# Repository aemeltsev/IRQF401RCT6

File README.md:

License
-------

IRQF401RCT6 schematic files and documentations are distributed under 
Creative Commons Attribution 4.0 International License.

Overview
--------
Simply dev. board based STM32F401RCT6. And includes in self: i2c eeprom memory and RS485 transceiver ic.

![PCB image][pcb_ray]

[pcb_ray]: https://github.com/aemeltsev/IRQF401RCT6/blob/master/doc/pcb_ray.png

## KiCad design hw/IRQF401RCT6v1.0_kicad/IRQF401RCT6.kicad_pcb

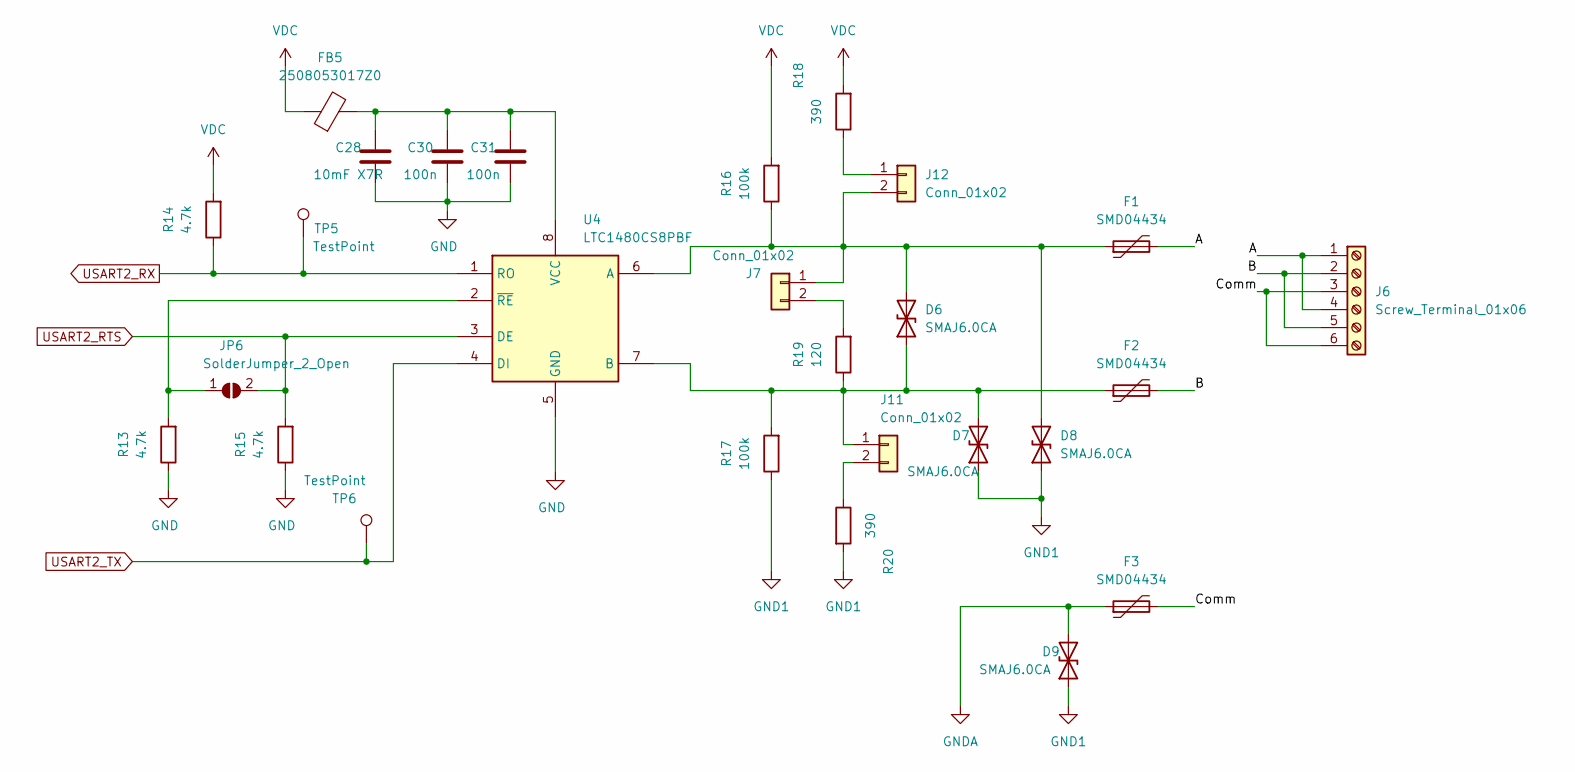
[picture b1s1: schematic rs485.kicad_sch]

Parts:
C28: 10mF X7R; C_1206_3216Metric
C30, C31: 100n; C_0805_2012Metric
D6, D7, D8, D9: SMAJ6.0CA; D_SMA
F1, F2, F3: SMD04434; Fuse_1812_4532Metric
FB5: 2508053017Z0; L_0805_2012Metric
J6: Screw_Terminal_01x06; PhoenixContact_MC_1,5_6-G-3.81_1x06_P3.81mm_Horizontal
J7, J11, J12: Conn_01x02; PinHeader_1x02_P2.54mm_Vertical
JP6: SolderJumper_2_Open; SolderJumper-2_P1.3mm_Open_TrianglePad1.0x1.5mm
R13, R14, R15: 4.7k; R_0805_2012Metric
R16, R17: 100k; R_0805_2012Metric
R18, R20: 390; R_0805_2012Metric
R19: 120; R_0805_2012Metric
TP5, TP6: TestPoint; TestPoint_Pad_D1.0mm
U4: LTC1480CS8PBF; SOIC-8_3.9x4.9mm_P1.27mm; Manufacturer_Part_Number LTC1480CS8PBF

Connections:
/RS485/A: F1.2, J6.1, J6.4
/RS485/B: F2.2, J6.2, J6.5
/RS485/Comm: F3.2, J6.3, J6.6
GND: C28.2, C30.2, C31.2, R13.1, R15.1, U4.5 (GND); also elsewhere on the board
GND1: D7.1 (A1), D8.1 (A1), D9.1 (A1), R17.1, R20.2
GNDA: D9.2 (A2), F3.1; also elsewhere on the board
unnamed: C28.1, C30.1, C31.1, FB5.2, U4.8 (VCC)
unnamed: D6.1 (A1), D7.2 (A2), F2.1, J11.1, R17.2, R19.1, U4.7 (B)
unnamed: D6.2 (A2), D8.2 (A2), F1.1, J7.1, J12.2, R16.1, U4.6 (A)
unnamed: J7.2, R19.2
unnamed: J11.2, R20.1
unnamed: J12.1, R18.1
unnamed: JP6.1 (A), R13.2, U4.2 (~RE)
USART2_RTS: JP6.2 (B), R15.2, U4.3 (DE); also elsewhere on the board
USART2_RX: R14.1, TP5.1, U4.1 (RO); also elsewhere on the board
USART2_TX: TP6.1, U4.4 (DI); also elsewhere on the board
VDC: FB5.1, R14.2, R16.2, R18.2; also elsewhere on the board

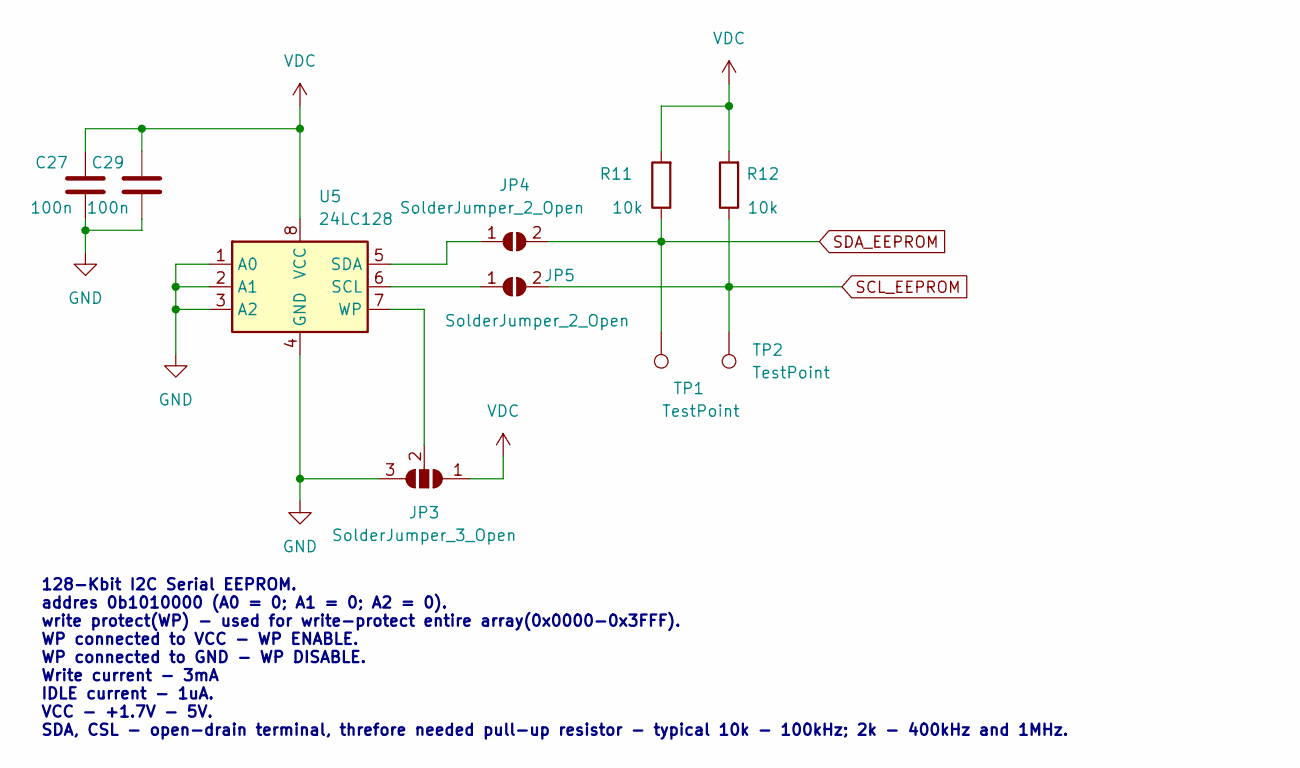
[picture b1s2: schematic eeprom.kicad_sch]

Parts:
C27, C29: 100n; C_0805_2012Metric
JP3: SolderJumper_3_Open; SolderJumper-3_P1.3mm_Open_RoundedPad1.0x1.5mm_NumberLabels
JP4, JP5: SolderJumper_2_Open; SolderJumper-2_P1.3mm_Open_TrianglePad1.0x1.5mm
R11, R12: 10k; R_0805_2012Metric
TP1, TP2: TestPoint; TestPoint_Pad_D1.0mm
U5: 24LC128; SOIC-8_3.9x4.9mm_P1.27mm

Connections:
GND: C27.2, C29.2, JP3.3 (B), U5.1 (A0), U5.2 (A1), U5.3 (A2), U5.4 (GND); also elsewhere on the board
unnamed: JP3.2 (C), U5.7 (WP)
unnamed: JP4.1 (A), U5.5 (SDA)
unnamed: JP5.1 (A), U5.6 (SCL)
SCL_EEPROM: JP5.2 (B), R12.1, TP2.1; also elsewhere on the board
SDA_EEPROM: JP4.2 (B), R11.1, TP1.1; also elsewhere on the board
VDC: C27.1, C29.1, JP3.1 (A), R11.2, R12.2, U5.8 (VCC); also elsewhere on the board

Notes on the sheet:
128-Kbit I2C Serial EEPROM. addres 0b1010000 (A0 = 0; A1 = 0; A2 = 0). write protect(WP) - used for write-protect entire array(0x0000-0x3FFF). WP connected to VCC - WP ENABLE. WP connected to GND - WP DISABLE. Write current - 3mA IDLE current - 1uA. VCC - +1.7V - 5V. SDA, CSL - open-drain terminal,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

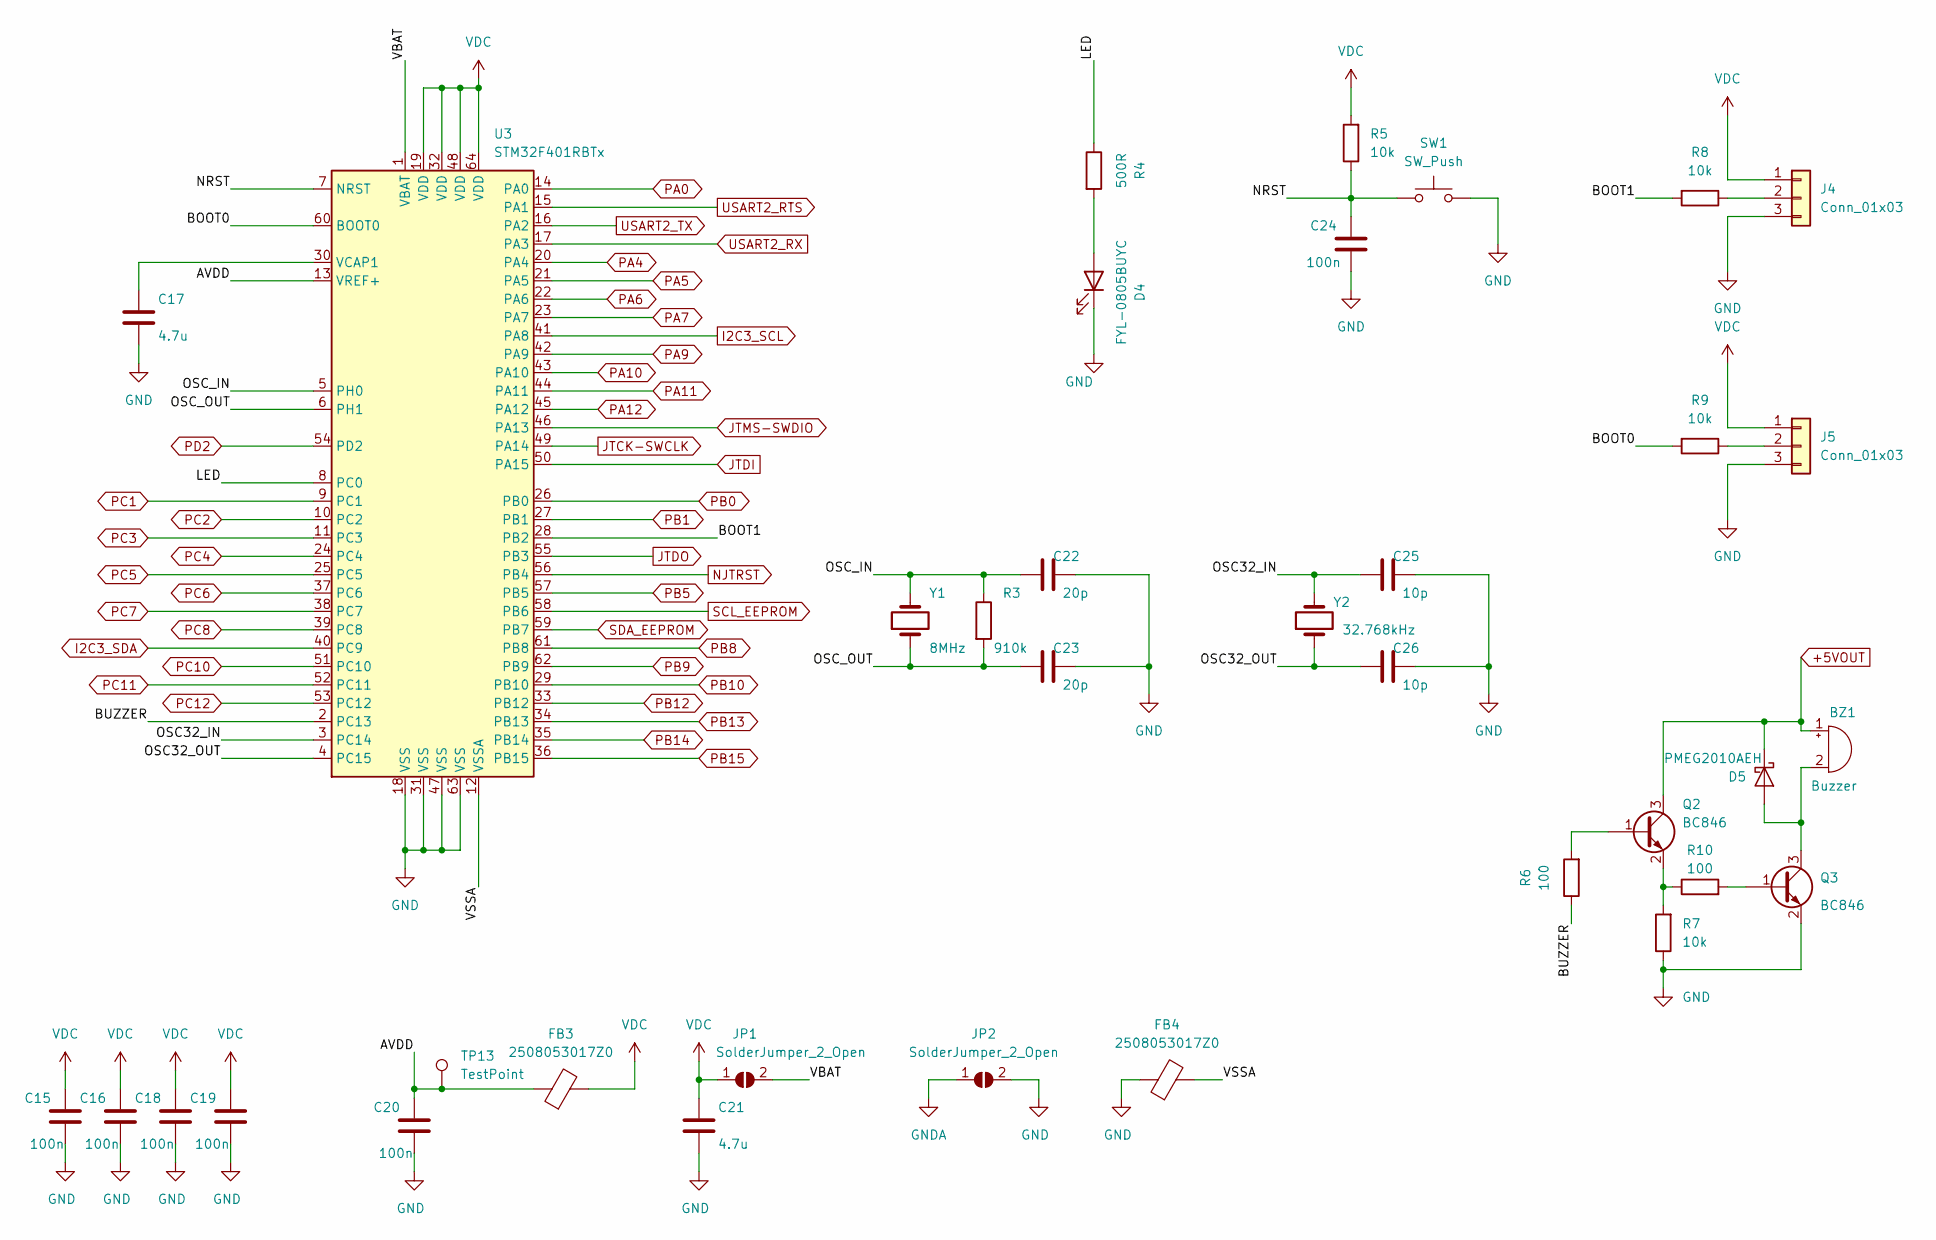
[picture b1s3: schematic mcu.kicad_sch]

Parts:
BZ1: Buzzer; Buzzer_12x9.5RM7.6
C15, C16, C18, C19, C20, C24: 100n; C_0805_2012Metric
C17, C21: 4.7u; C_1206_3216Metric
C22, C23: 20p; C_0805_2012Metric
C25, C26: 10p; C_0805_2012Metric
D4: FYL-0805BUYC; LED_0805_2012Metric
D5: PMEG2010AEH; D_SOD-123F
FB3, FB4: 2508053017Z0; L_0805_2012Metric
J4, J5: Conn_01x03; PinHeader_1x03_P2.54mm_Vertical
JP1, JP2: SolderJumper_2_Open; SolderJumper-2_P1.3mm_Open_TrianglePad1.0x1.5mm
Q2, Q3: BC846; SOT-23
R3: 910k; R_0805_2012Metric
R4: 500R; R_0805_2012Metric
R5, R7, R8, R9: 10k; R_0805_2012Metric
R6, R10: 100; R_0805_2012Metric
SW1: SW_Push; SW_DIP_SPSTx01_Slide_6.7x4.1mm_W7.62mm_P2.54mm_LowProfile
TP13: TestPoint; TestPoint_Pad_D1.0mm
U3: STM32F401RBTx; LQFP-64_10x10mm_P0.5mm
Y1: 8MHz; Crystal_HC49-4H_Vertical
Y2: 32.768kHz; Crystal_C26-LF_D2.1mm_L6.5mm_Horizontal_1EP_style1

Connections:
+5VOUT: BZ1.1 (-), D5.1 (K), Q2.3 (C); also elsewhere on the board
/MCU/AVDD: C20.1, FB3.1, TP13.1, U3.13 (VREF+)
/MCU/BOOT0: R9.2, U3.60 (BOOT0)
/MCU/BOOT1: R8.2, U3.28 (PB2)
/MCU/BUZZER: R6.1, U3.2 (PC13)
/MCU/LED: R4.1, U3.8 (PC0)
/MCU/NRST: C24.1, R5.1, SW1.1, U3.7 (NRST)
/MCU/OSC32_IN: C25.1, U3.3 (PC14), Y2.2
/MCU/OSC32_OUT: C26.1, U3.4 (PC15), Y2.1
/MCU/OSC_IN: C22.1, R3.1, U3.5 (PH0), Y1.2
/MCU/OSC_OUT: C23.1, R3.2, U3.6 (PH1), Y1.1
/MCU/VBAT: JP1.2 (B), U3.1 (VBAT)
/MCU/VSSA: FB4.2, U3.12 (VSSA)
GND: C15.2, C16.2, C17.2, C18.2, C19.2, C20.2, C21.2, C22.2, C23.2, C24.2, C25.2, C26.2, D4.1 (K), FB4.1, J4.3, J5.3, JP2.2 (B), Q3.2 (E), R7.1, SW1.2, U3.18 (VSS), U3.31 (VSS), U3.47 (VSS), U3.63 (VSS); also elsewhere on the board
GNDA: JP2.1 (A); also elsewhere on the board
I2C3_SCL: U3.41 (PA8); also elsewhere on the board
I2C3_SDA: U3.40 (PC9); also elsewhere on the board
JTCK-SWCLK: U3.49 (PA14); also elsewhere on the board
JTDI: U3.50 (PA15); also elsewhere on the board
JTDO: U3.55 (PB3); also elsewhere on the board
JTMS-SWDIO: U3.46 (PA13); also elsewhere on the board
NJTRST: U3.56 (PB4); also elsewhere on the board
unnamed: BZ1.2 (+), D5.2 (A), Q3.3 (C)
unnamed: C17.1, U3.30 (VCAP1)
unnamed: D4.2 (A), R4.2
unnamed: J4.2, R8.1
unnamed: J5.2, R9.1
unnamed: Q2.1 (B), R6.2
unnamed: Q2.2 (E), R7.2, R10.1
unnamed: Q3.1 (B), R10.2
PA0: U3.14 (PA0); also elsewhere on the board
PA4: U3.20 (PA4); also elsewhere on the board
PA5: U3.21 (PA5); also elsewhere on the board
PA6: U3.22 (PA6); also elsewhere on the board
PA7: U3.23 (PA7); also elsewhere on the board
PA9: U3.42 (PA9); also elsewhere on the board
PA10: U3.43 (PA10); also elsewhere on the board
PA11: U3.44 (PA11); also elsewhere on the board
PA12: U3.45 (PA12); also elsewhere on the board
PB0: U3.26 (PB0); also elsewhere on the board
PB1: U3.27 (PB1); also elsewhere on the board
PB5: U3.57 (PB5); also elsewhere on the board
PB8: U3.61 (PB8); also elsewhere on the board
PB9: U3.62 (PB9); also elsewhere on the board
PB10: U3.29 (PB10); also elsewhere on the board
PB12: U3.33 (PB12); also elsewhere on the board
PB13: U3.34 (PB13); also elsewhere on the board
PB14: U3.35 (PB14); also elsewhere on the board
PB15: U3.36 (PB15); also elsewhere on the board
PC1: U3.9 (PC1); also elsewhere on the board
PC2: U3.10 (PC2); also elsewhere on the board
PC3: U3.11 (PC3); also elsewhere on the board
PC4: U3.24 (PC4); also elsewhere on the board
PC5: U3.25 (PC5); also elsewhere on the board
PC6: U3.37 (PC6); also elsewhere on the board
PC7: U3.38 (PC7); also elsewhere on the board
PC8: U3.39 (PC8); also elsewhere on the board
PC10: U3.51 (PC10); also elsewhere on the board
PC11: U3.52 (PC11); also elsewhere on the board
PC12: U3.53 (PC12); also elsewhere on the board
PD2: U3.54 (PD2); also elsewhere on the board
SCL_EEPROM: U3.58 (PB6); also elsewhere on the board
SDA_EEPROM: U3.59 (PB7); also elsewhere on the board
USART2_RTS: U3.15 (PA1); also elsewhere on the board
USART2_RX: U3.17 (PA3); also elsewhere on the board
USART2_TX: U3.16 (PA2); also elsewhere on the board
VDC: C15.1, C16.1, C18.1, C19.1, C21.1, FB3.2, J4.1, J5.1, JP1.1 (A), R5.2, U3.19 (VDD), U3.32 (VDD), U3.48 (VDD), U3.64 (VDD); also elsewhere on the board

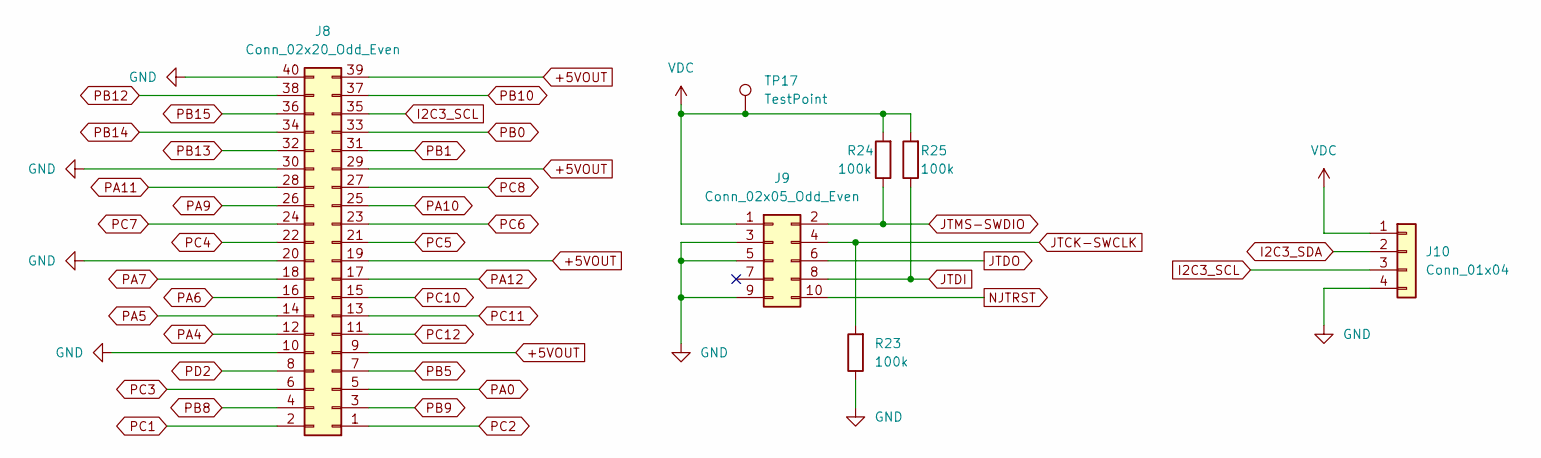
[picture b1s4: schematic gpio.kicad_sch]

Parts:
J8: Conn_02x20_Odd_Even; PinSocket_2x20_P2.54mm_Horizontal
J9: Conn_02x05_Odd_Even; PinHeader_2x05_P2.54mm_Vertical
J10: Conn_01x04; PinHeader_1x04_P2.54mm_Vertical
R23, R24, R25: 100k; R_0805_2012Metric
TP17: TestPoint; TestPoint_Pad_D1.0mm

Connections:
+5VOUT: J8.9, J8.19, J8.29, J8.39; also elsewhere on the board
GND: J8.10, J8.20, J8.30, J8.40, J9.3, J9.5, J9.9, J10.4, R23.1; also elsewhere on the board
I2C3_SCL: J8.35, J10.3; also elsewhere on the board
I2C3_SDA: J10.2; also elsewhere on the board
JTCK-SWCLK: J9.4, R23.2; also elsewhere on the board
JTDI: J9.8, R25.1; also elsewhere on the board
JTDO: J9.6; also elsewhere on the board
JTMS-SWDIO: J9.2, R24.1; also elsewhere on the board
NJTRST: J9.10; also elsewhere on the board
PA0: J8.5; also elsewhere on the board
PA4: J8.12; also elsewhere on the board
PA5: J8.14; also elsewhere on the board
PA6: J8.16; also elsewhere on the board
PA7: J8.18; also elsewhere on the board
PA9: J8.26; also elsewhere on the board
PA10: J8.25; also elsewhere on the board
PA11: J8.28; also elsewhere on the board
PA12: J8.17; also elsewhere on the board
PB0: J8.33; also elsewhere on the board
PB1: J8.31; also elsewhere on the board
PB5: J8.7; also elsewhere on the board
PB8: J8.4; also elsewhere on the board
PB9: J8.3; also elsewhere on the board
PB10: J8.37; also elsewhere on the board
PB12: J8.38; also elsewhere on the board
PB13: J8.32; also elsewhere on the board
PB14: J8.34; also elsewhere on the board
PB15: J8.36; also elsewhere on the board
PC1: J8.2; also elsewhere on the board
PC2: J8.1; also elsewhere on the board
PC3: J8.6; also elsewhere on the board
PC4: J8.22; also elsewhere on the board
PC5: J8.21; also elsewhere on the board
PC6: J8.23; also elsewhere on the board
PC7: J8.24; also elsewhere on the board
PC8: J8.27; also elsewhere on the board
PC10: J8.15; also elsewhere on the board
PC11: J8.13; also elsewhere on the board
PC12: J8.11; also elsewhere on the board
PD2: J8.8; also elsewhere on the board
VDC: J9.1, J10.1, R24.2, R25.2, TP17.1; also elsewhere on the board

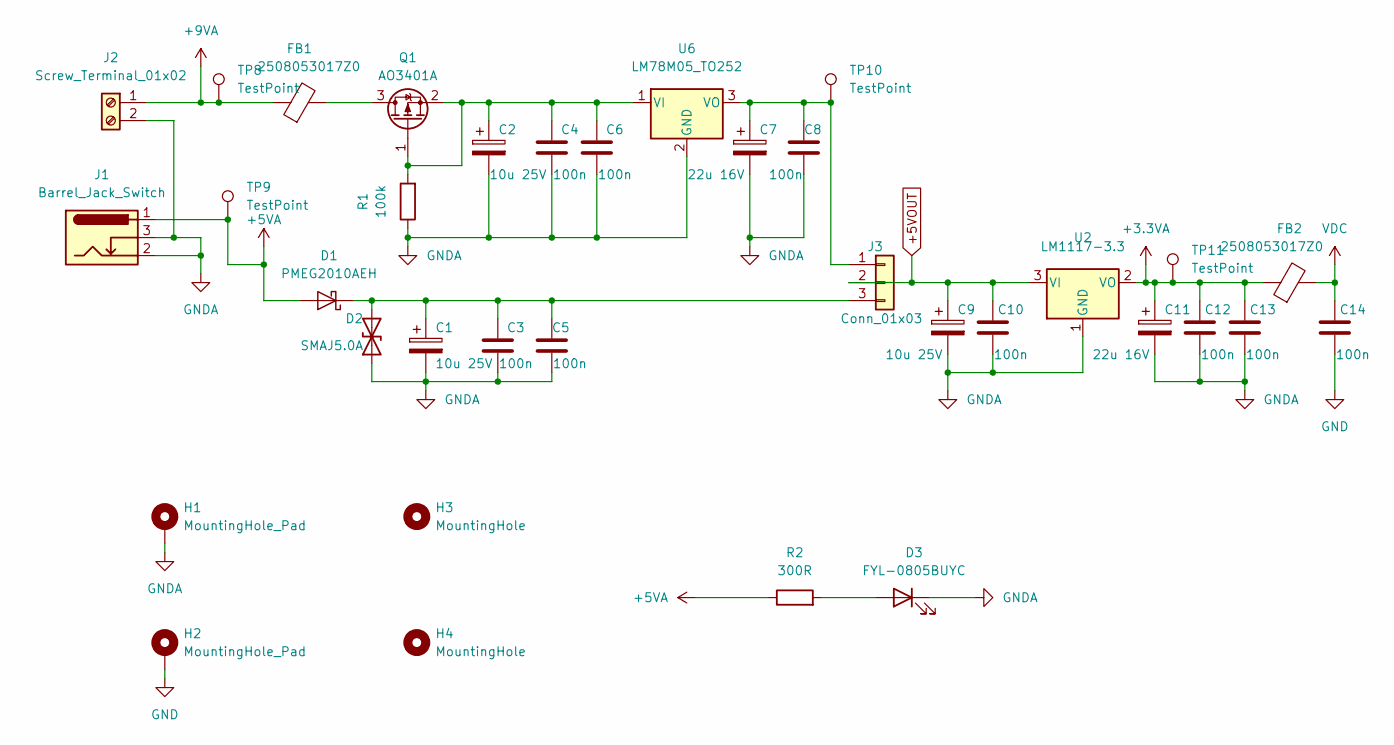
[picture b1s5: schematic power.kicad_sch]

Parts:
C1, C2, C9: 10u 25V; CP_Elec_4x5.4
C3, C4, C5, C6, C8, C10, C12, C13, C14: 100n; C_0805_2012Metric
C7, C11: 22u 16V; CP_Elec_6.3x5.4
D1: PMEG2010AEH; D_SOD-123F
D2: SMAJ5.0A; D_SMA
D3: FYL-0805BUYC; LED_0805_2012Metric
FB1, FB2: 2508053017Z0; L_0805_2012Metric
H1, H2: MountingHole_Pad; MountingHole_2.5mm_Pad
H3, H4: MountingHole; MountingHole_2.5mm
J1: Barrel_Jack_Switch; BarrelJack_GCT_DCJ200-10-A_Horizontal
J2: Screw_Terminal_01x02; PhoenixContact_MC_1,5_2-G-3.81_1x02_P3.81mm_Horizontal
J3: Conn_01x03; PinHeader_1x03_P2.54mm_Vertical
Q1: AO3401A; SOT-23
R1: 100k; R_0805_2012Metric
R2: 300R; R_0805_2012Metric
TP8, TP9, TP10, TP11: TestPoint; TestPoint_Pad_D1.0mm
U2: LM1117-3.3; SOT-223
U6: LM78M05_TO252; TO-252-2

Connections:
+3.3VA: C11.1, C12.1, C13.1, FB2.1, TP11.1, U2.2 (VO)
+5VA: D1.2 (A), J1.1, R2.1, TP9.1
+5VOUT: C9.1, C10.1, J3.2, U2.3 (VI); also elsewhere on the board
+9VA: FB1.1, J2.1, TP8.1
GND: C14.2, H2.1; also elsewhere on the board
GNDA: C1.2, C2.2, C3.2, C4.2, C5.2, C6.2, C7.2, C8.2, C9.2, C10.2, C11.2, C12.2, C13.2, D2.1 (A1), D3.1 (K), H1.1, J1.2, J1.3, J2.2, R1.1, U2.1 (GND), U6.2 (GND); also elsewhere on the board
unnamed: C1.1, C3.1, C5.1, D1.1 (K), D2.2 (A2), J3.3
unnamed: C2.1, C4.1, C6.1, Q1.1 (G), Q1.2 (S), R1.2, U6.1 (VI)
unnamed: C7.1, C8.1, J3.1, TP10.1, U6.3 (VO)
unnamed: D3.2 (A), R2.2
unnamed: FB1.2, Q1.3 (D)
VDC: C14.1, FB2.2; also elsewhere on the board

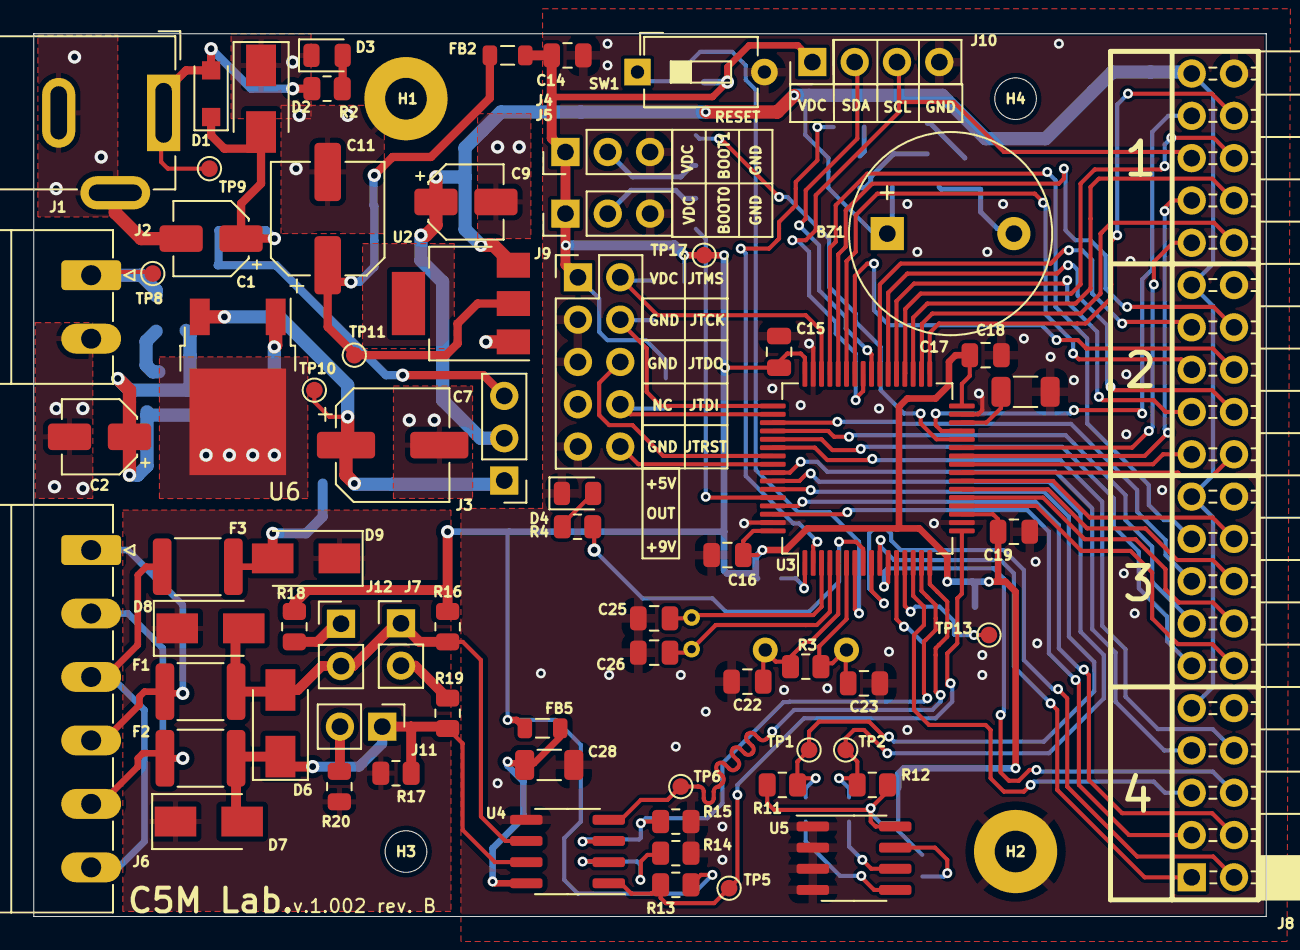
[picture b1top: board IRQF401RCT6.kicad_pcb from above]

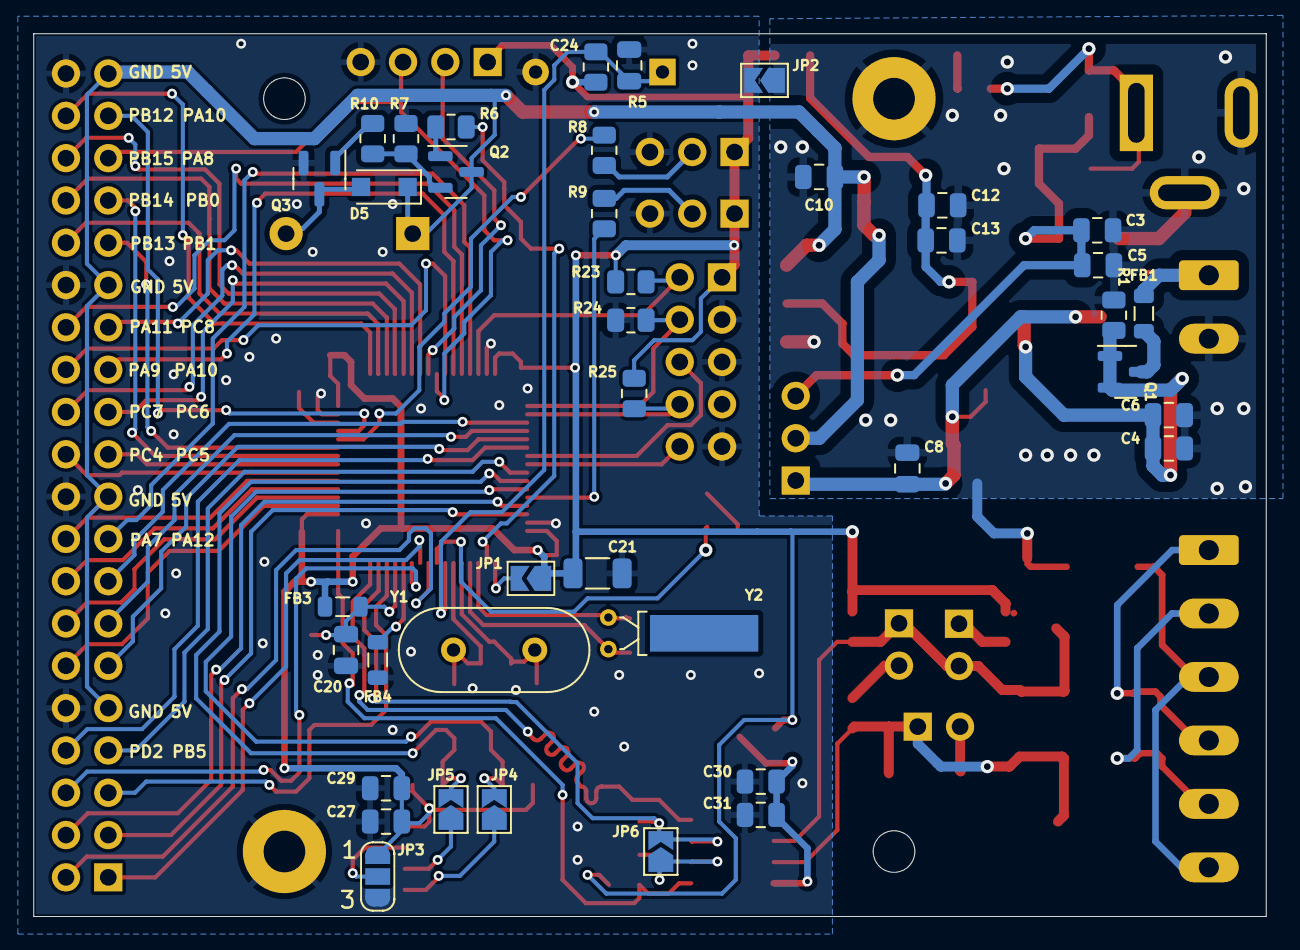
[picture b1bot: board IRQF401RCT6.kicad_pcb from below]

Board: 2 copper layers, 74.0 x 53.0 mm, 115 parts (40 on the bottom side), 89 nets.

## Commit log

2017-10-18 :tada: Added .gitattributes & .gitignore files
2017-10-18 Add fifes
    Add schematic & doc files
2019-01-13 Create README.md
    add Readme
2019-01-13 Add files
    Add project files, data files and image. Include revise history.
2019-01-13 Rename
    Rename to IRQF401RCT6v1.002.revB.png
2019-01-13 Update README.md
    Add BRD image file
2019-01-13 Update README.md
    Update
2020-03-10 rev
    New revision
2024-01-12 Upgrage all
    Project update, using Kicad
